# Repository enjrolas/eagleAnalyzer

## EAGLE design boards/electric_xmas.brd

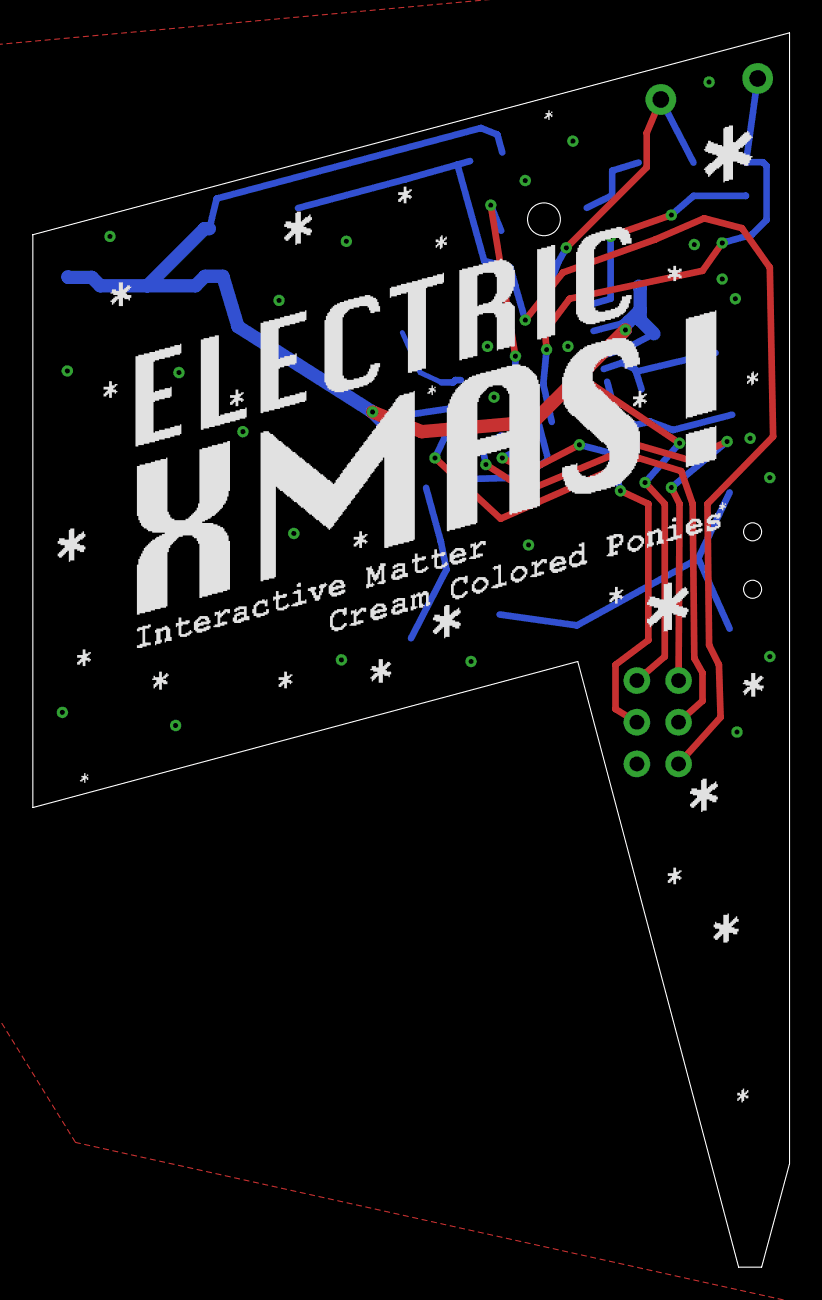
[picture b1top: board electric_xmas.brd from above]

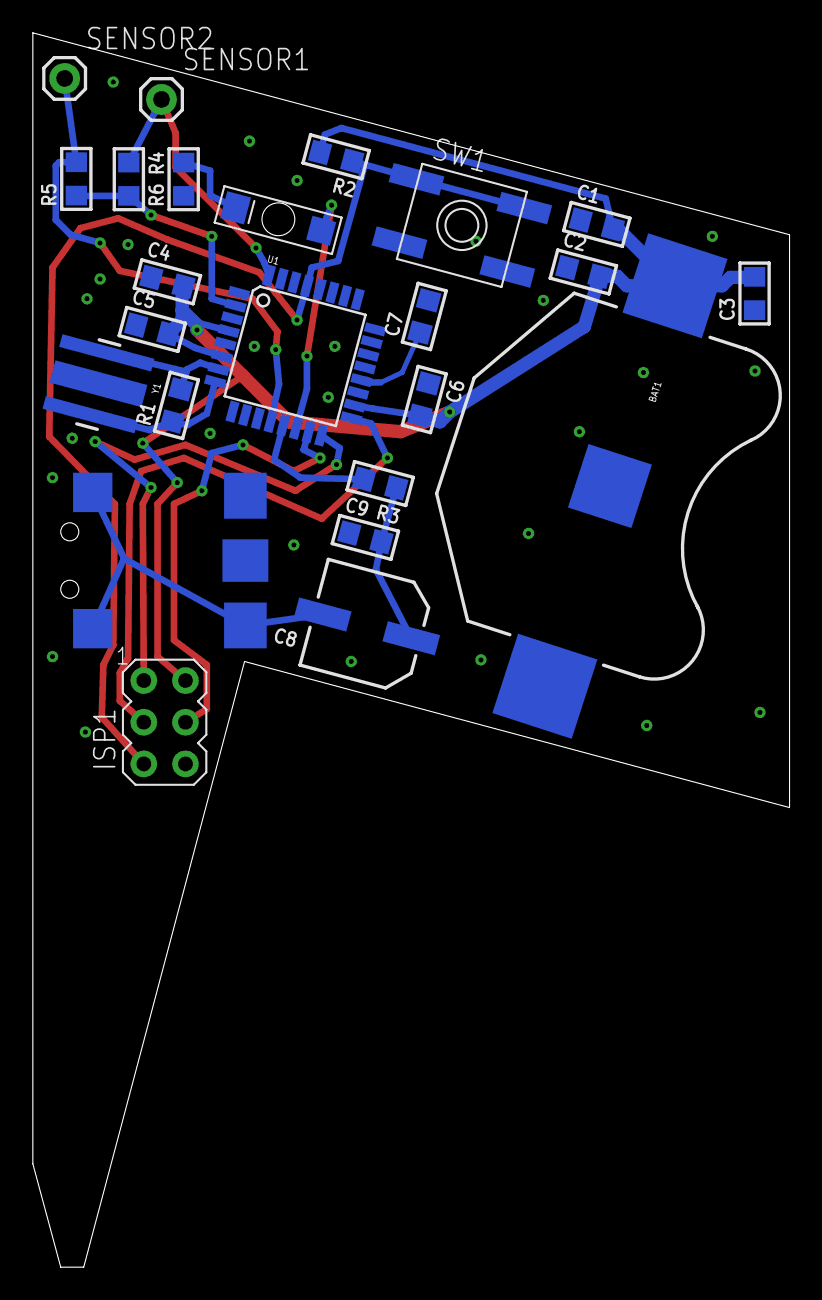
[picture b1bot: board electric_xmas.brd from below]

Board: 2 copper layers, 46.1 x 75.2 mm, 26 parts (24 on the bottom side), 17 nets.

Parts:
BAT1: BATTCON_20MM
C1, C2, C3: 10µF; C0805
C4, C5, C6, C7, C9: 100nF; C0805
C8: 100µF; CSV-D
ISP1: AVRISP-6; AVRISP
LED1: LUMEX_GW_BOTTOM
R1: 1M; R0805
R2: 10k; R0805
R3, R6: 2k2; R0805
R4, R5: 3M3; R0805
SENSOR1, SENSOR2: M01PTH; 1X01
SW1: EVQQ2; EVQ-Q2
U1: ATMEGA328P; TQFP32-08
U2: LUMBERGRC-5325A
U$2: OUTLINE
U$3: PRINT
Y1: RESONATORSMD; RESONATOR-SMD

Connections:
!RESET: ISP1.5, R2.1, SW1.B, SW1.B', U1.29
GND: BAT1.2, C1.1, C2.1, C3.1, C4.1, C5.1, C6.1, C7.2, C9.1, ISP1.6, R6.1, SW1.A, SW1.A', U1.3, U1.5, U1.21, U2.1, U2.2, Y1.2
LED: LED1.A, U1.14
MISO: ISP1.1, U1.16
MOSI: ISP1.4, U1.15
unnamed: R1.2, U1.7, Y1.1
unnamed: R1.1, U1.8, Y1.3
unnamed: LED1.C, R6.2
unnamed: C8.-, U2.3, U2.4@1, U2.4@2
unnamed: C7.1, U1.20
unnamed: C8.+, C9.2, R3.1
SCK: ISP1.3, U1.17
SENSOR1: R4.1, SENSOR1.1, U1.32
SENSOR2: R5.2, SENSOR2.1, U1.12
SENSOR_C: R4.2, R5.1, U1.2
SOUND_OUT: R3.2, U1.13
VCC: BAT1.1, C1.2, C2.2, C3.2, C4.2, C5.2, C6.2, ISP1.2, R2.2, U1.4, U1.6, U1.18

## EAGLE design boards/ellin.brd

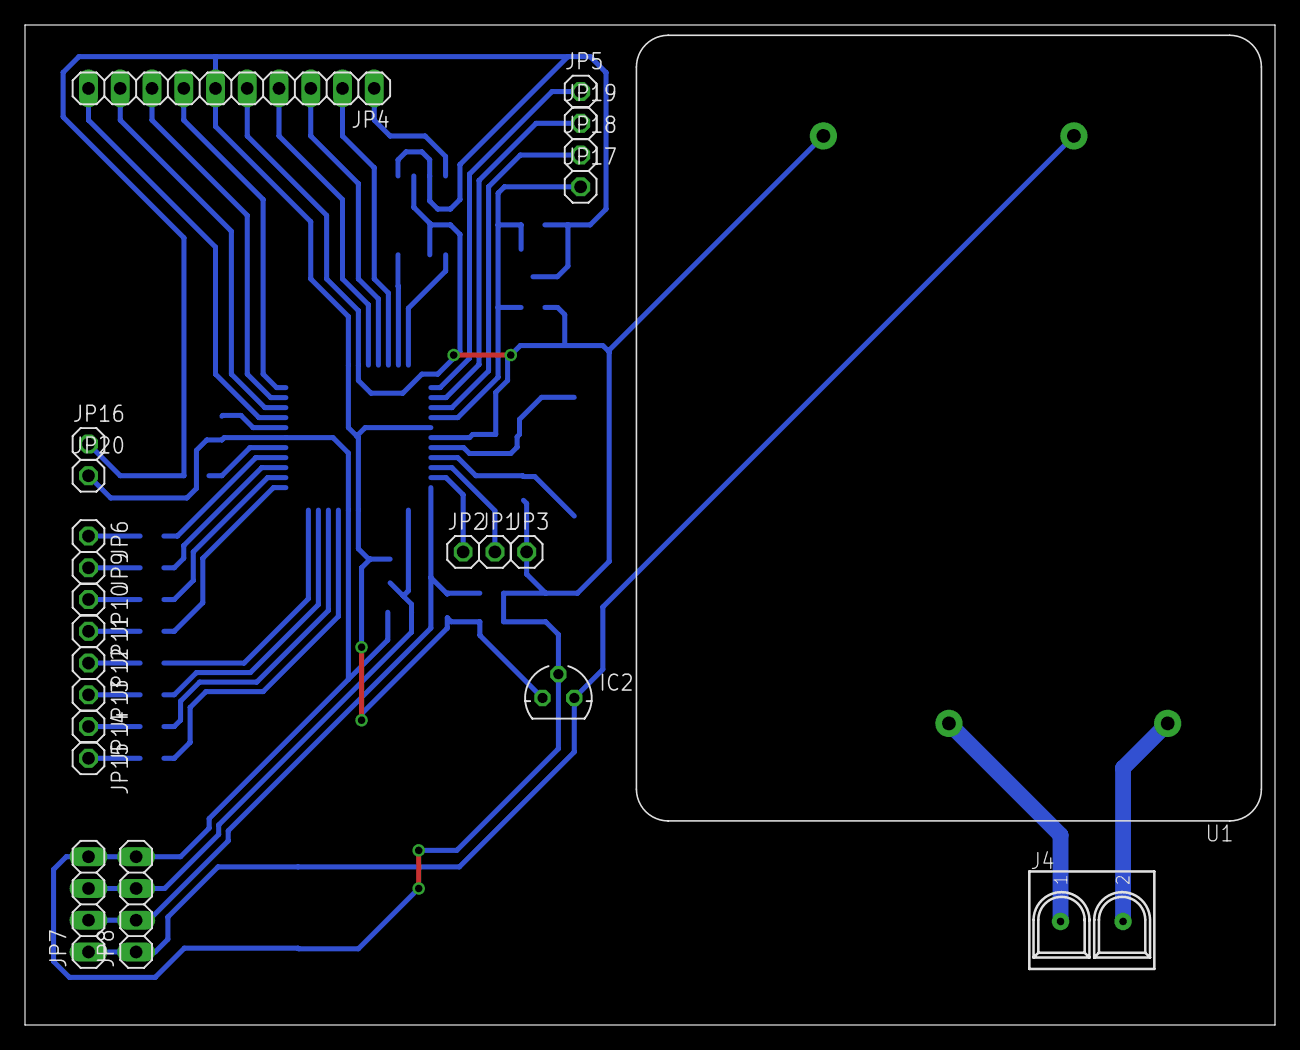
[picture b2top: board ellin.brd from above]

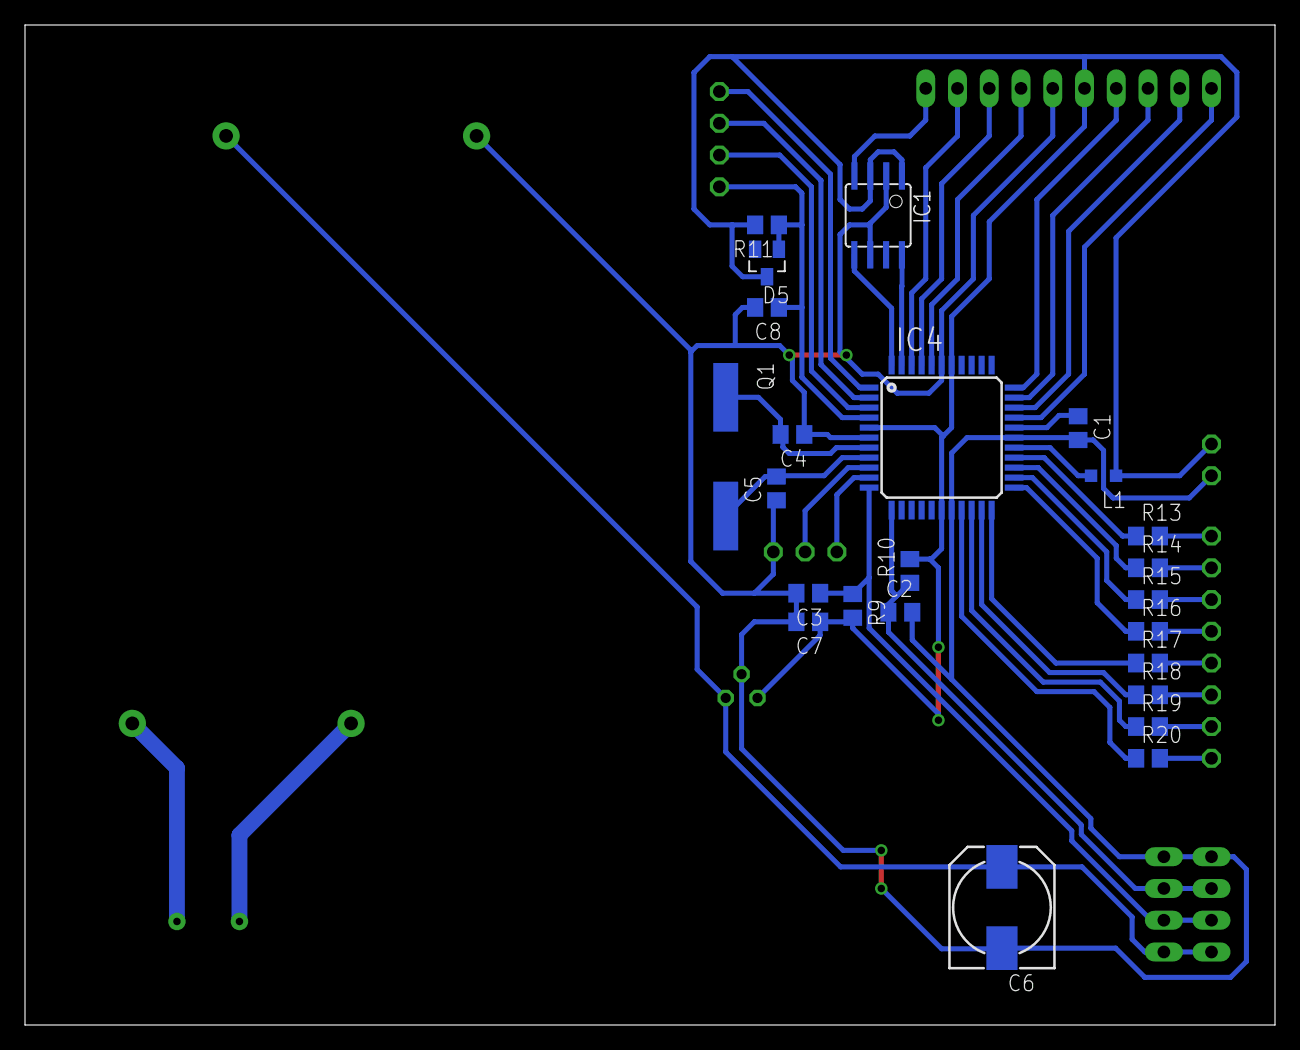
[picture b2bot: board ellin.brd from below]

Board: 2 copper layers, 100.0 x 80.0 mm, 47 parts (24 on the bottom side), 43 nets.

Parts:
C1, C8: 0.1uF; C0805
C2, C3, C7: 22nF; C0805
C4, C5: 22pF; C0805
C6: 10uF; 140CLH-0810
D5: BAS16; SOT23
IC1: MCP4011; SOIC8
IC2: 78L05; 78LXX
IC4: MEGA16-A; TQFP44
J4: DG126-5.0
JP1: RXD; 1X01
JP2: TXD; 1X01
JP3: GND; 1X01
JP4: LCD; 1X10
JP5, JP6, JP9, JP10, JP11, JP12, JP13, JP14, JP15, JP16, JP17, JP18, JP19, JP20: 1X01
JP7, JP8: 1X04
L1: L2012C
Q1: 20MHz; CSM-7X-DU
R9, R10, R11: 10k; R0805
R13, R14, R15, R16, R17, R18, R19, R20: 100; R0805
U1: PM-05

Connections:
+12V: C6.+, IC2.IN, JP7.1, JP8.1, U1.V+
AREF: C1.1, IC4.29
AVCC: IC4.27, L1.2
DATA4: IC4.23, R16.1
DATA5: IC4.24, R15.1
DATA6: IC4.25, R14.1
DATA7: IC4.26, R13.1
DB4: IC4.33, JP4.7
DB5: IC4.32, JP4.8
DB6: IC4.31, JP4.9
DB7: IC4.30, JP4.10
DIG_POT: IC1.8, IC4.43
EN: IC4.40, JP4.4
GND: C1.2, C2.2, C3.2, C4.1, C5.1, C6.-, C7.2, C8.2, IC1.2, IC1.6, IC2.GND, IC4.6, IC4.18, IC4.28, IC4.39, JP3.1, JP4.5, JP7.4, JP8.4, JP20.1, U1.V-
KEYB0: IC4.19, R20.1
KEYB1: IC4.20, R19.1
KEYB2: IC4.21, R18.1
KEYB3: IC4.22, R17.1
MISO: IC4.2, JP19.1
MOSI: IC4.1, JP5.1
unnamed: JP6.1, R13.2
unnamed: J4.1, U1.AC/N
unnamed: J4.2, U1.AC/L
unnamed: JP9.1, R14.2
unnamed: JP10.1, R15.2
unnamed: JP11.1, R16.2
unnamed: JP12.1, R17.2
unnamed: JP13.1, R18.2
unnamed: JP14.1, R19.2
unnamed: JP15.1, R20.2
PHASE_A: C3.1, IC4.11, JP7.2, JP8.2, R9.1
PHASE_B: C2.1, IC4.12, JP7.3, JP8.3, R10.1
POT_CS: IC1.5, IC4.44
R/!W!: IC4.41, JP4.3
RS: IC4.42, JP4.2
RST: C8.1, D5.1, IC4.4, JP17.1, R11.1
RXD: IC4.9, JP1.1
SCK: IC4.3, JP18.1
TXD: IC4.10, JP2.1
VCC: C7.1, D5.3, IC1.1, IC1.3, IC2.OUT, IC4.5, IC4.17, IC4.38, JP4.6, JP16.1, L1.1, R9.2, R10.2, R11.2
W: IC1.4, JP4.1
XTAL1: C5.2, IC4.8, Q1.2
XTAL2: C4.2, IC4.7, Q1.1

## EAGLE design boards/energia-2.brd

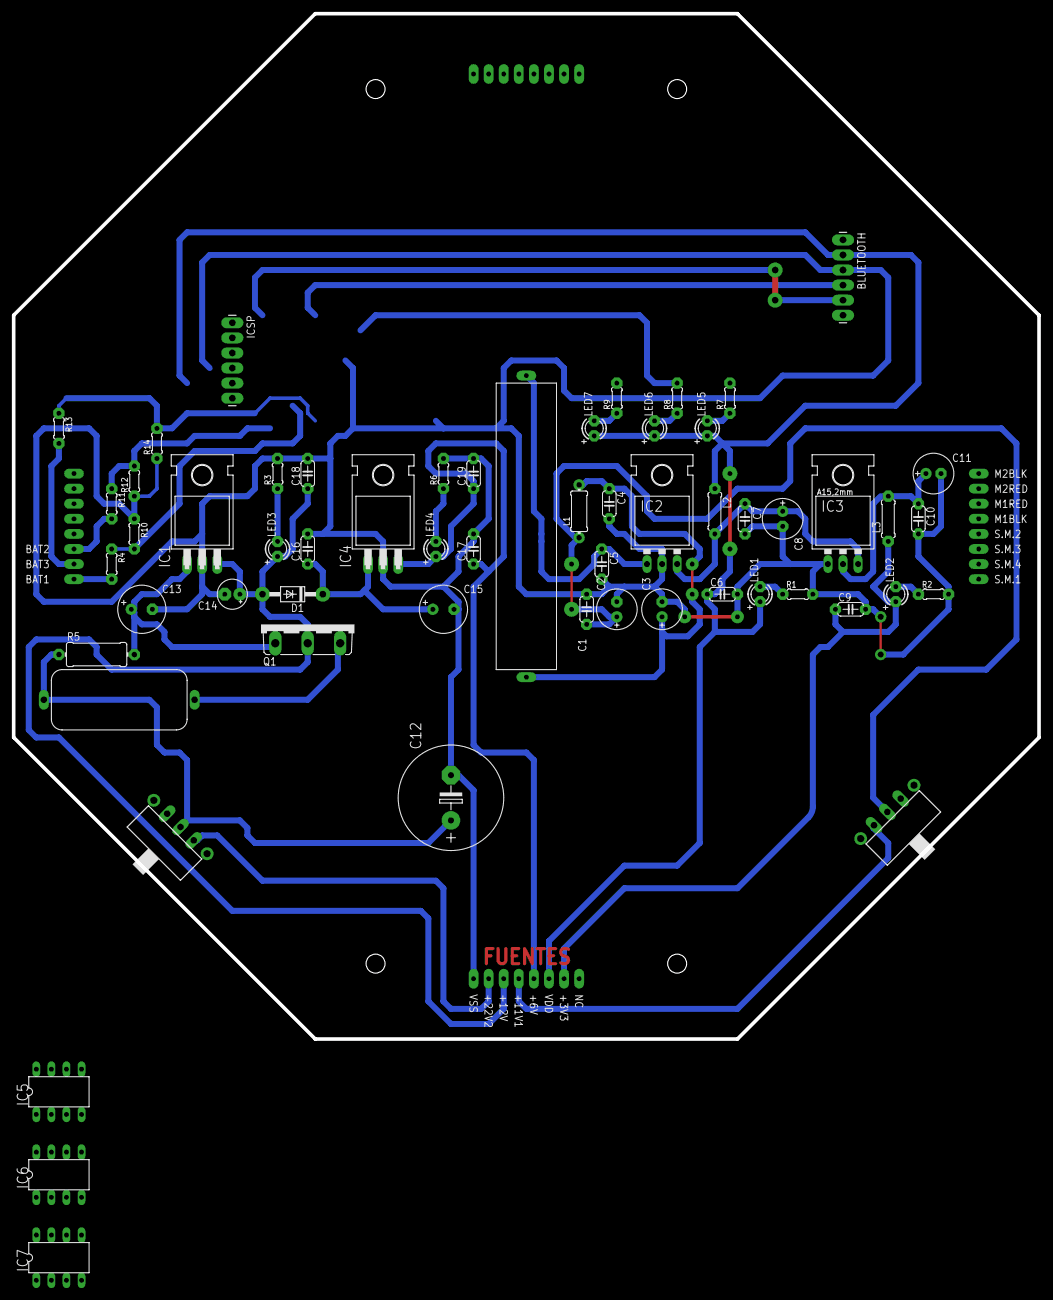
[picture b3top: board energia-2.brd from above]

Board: 2 copper layers, 172.7 x 172.7 mm, 59 parts (0 on the bottom side), 29 nets.

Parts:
BLUETOOTH: 1X06_LONGPADS
C1, C4, C5, C6, C7, C9, C10, C16, C17, C18, C19: 0.1uf; C050-024X044
C2: 470uf; E2,5-7
C3: 100uf; E2,5-7
C8, C11: 22uf; E2,5-7
C12: 3300uf; E7,5-18
C13, C15: 470uf; E3,5-8
C14: 10uf; E2,5-5
D1: 1N4007; DO41-10
IC1: 7812T; TO220H
IC2: 7805; TO-220-ALT
IC3: AZ1117; 78XXL
IC4: 7806T; TO220H
IC5, IC6, IC7: PIC12F675P; DIL8
ICSP: 1X06_LONGPADS
L1: 100uH; TFI0307
L2, L3: 100uH; 0207/7
LED1, LED3: ROJO; LED3MM
LED2, LED4: VERDE; LED3MM
LED5, LED6, LED7: RED; LED3MM
Q1: TIP2955; TOP3AV
R1, R3: 2k2; 0204/5
R2, R6: 680; 0204/5
R4, R11, R13: 20K; 0204/5
R5: 2W100R; 0411/12
R7, R8, R9: 470; 0204/5
R10, R12, R14: 15K; 0204/5
S1, S2: SWITCH; TL3XYO
U$1: BASE
U$6: 5W0.1RJ; RES-22X10
U$9: 10W 5R6J; RES-49X10

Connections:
+3V3: C9.1, L3.1, LED2.A, U$1.PIN22
+6V: C17.1, C19.1, IC4.3, LED4.A, U$1.PIN20
+11V1: S1.3, U$1.PIN19
+12V: C14.+, C18.1, D1.A, IC1.3, LED3.A, Q1.C, U$1.PIN18
+22V: S2.1, U$1.PIN17
AN0: R4.1, R10.2
AN1: R11.1, R12.2
AN2: R13.1, R14.2
unnamed: C1.1, C2.+, L1.1, S1.2
unnamed: LED3.K, R3.1
unnamed: C12.+, R5.1, S2.2, U$6.P$1
unnamed: Q1.E, U$6.P$2
unnamed: C13.+, IC1.1, Q1.B, R5.2
unnamed: LED4.K, R6.1
unnamed: C5.1, IC2.IN, U$9.P$2
unnamed: C3.+, C4.1, L1.2, U$9.P$1
unnamed: C7.1, C8.+, IC2.OUT, IC3.OUT, L2.2
unnamed: C15.+, C16.1, D1.C, IC4.1
unnamed: LED1.K, R1.1
unnamed: LED5.K, R7.1
unnamed: LED7.K, R9.1
unnamed: C10.1, C11.+, IC3.GND, L3.2
unnamed: LED2.K, R2.1
unnamed: LED6.K, R8.1
SENSE1: R4.2, U$1.PIN15
SENSE2: R11.2, U$1.PIN13
SENSE3: R13.2, U$1.PIN14
VDD: BLUETOOTH.2, C6.1, IC5.1, IC6.1, IC7.1, L2.1, LED1.A, LED5.A, LED6.A, LED7.A, U$1.PIN21
VSS: BLUETOOTH.3, C1.2, C2.-, C3.-, C4.2, C5.2, C6.2, C7.2, C8.-, C9.2, C10.2, C11.-, C12.-, C13.-, C14.-, C15.-, C16.2, C17.2, C18.2, C19.2, IC1.2, IC2.GND, IC3.IN, IC4.2, IC5.8, IC6.8, IC7.8, R1.2, R2.2, R3.2, R6.2, R10.1, R12.1, R14.1, U$1.PIN16

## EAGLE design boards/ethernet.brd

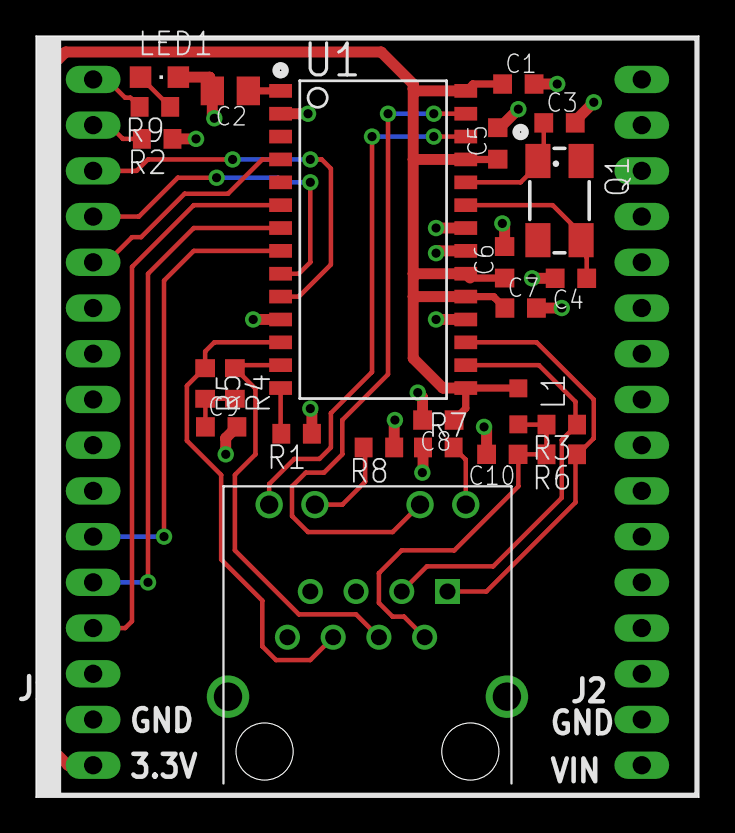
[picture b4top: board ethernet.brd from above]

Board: 2 copper layers, 36.8 x 42.3 mm, 26 parts (0 on the bottom side), 25 nets.

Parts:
C1, C5, C6, C7, C8, C9, C10: 0.1 uF; C0603K
C2: 22 uF; C0805K
C3, C4: 18 pF; C0603K
J1, J2: MA016-1
J3: SI-50154
L1: Ferrite 80mA; L2012C
LED1: Green; CHIPLED_0805
Q1: 25 MHz; CTS406
R1: 2.32k 1%; R0603
R2, R7, R8, R9: 150; R0603
R3, R4, R5, R6: 50; R0603
U1: ENC28J60; SO-28W

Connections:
GND: C1.2, C2.2, C3.2, C4.2, C5.2, C6.2, C7.2, C8.2, C9.2, C10.2, J1.2, J1.8, J2.2, J2.8, J3.P$8, LED1.C, R1.1, R2.1, R7.1, R8.1, U1.2, U1.11, U1.18, U1.21, U1.22
GPIO0: J1.16, R9.2
GPIO1: J1.15, R2.2
GPIO2: J1.14, U1.10
GPIO3: J1.13, U1.9
GPIO4_INT0: J1.12, U1.4
LEDA: J3.P$10, U1.27
LEDA-: J3.P$9, R7.2
LEDB: J3.P$12, U1.26
LEDB-: J3.P$11, R8.2
MISO: J1.4, U1.6
MOSI: J1.5, U1.7
unnamed: LED1.A, R9.1
RBIAS: R1.2, U1.14
SCK: J1.6, U1.8
TCT: C10.1, J3.P$2, L1.2, R3.2, R6.2
TPIN+: J3.P$4, R4.1, U1.13
TPIN-: J3.P$6, R5.1, U1.12
TPIN_CAP: C9.1, R4.2, R5.2
TPOUT+: J3.P$1, R6.1, U1.17
TPOUT-: J3.P$3, R3.1, U1.16
VCAP: C2.1, U1.1
VCC: C1.1, C5.1, C6.1, C7.1, C8.1, J1.1, L1.1, U1.15, U1.19, U1.20, U1.25, U1.28
XTAL3: C3.1, Q1.1, U1.24
XTAL4: C4.1, Q1.3, U1.23

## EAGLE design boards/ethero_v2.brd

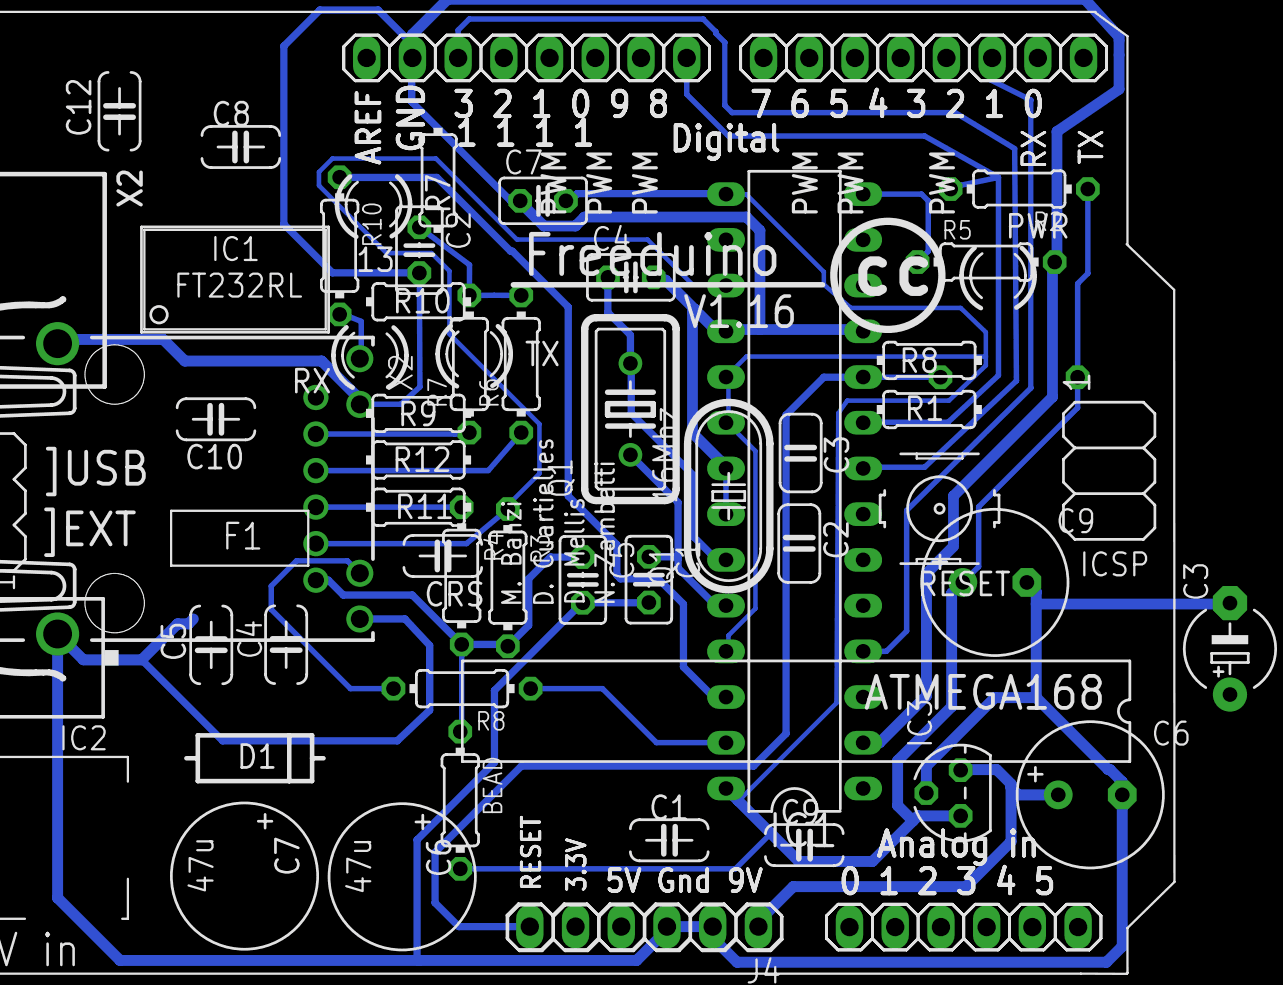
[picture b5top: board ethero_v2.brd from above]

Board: 2 copper layers, 26 parts (1 on the bottom side), 23 nets.

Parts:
BEAD: 18; 0204/7
C1, C4: 18pF; C025-025X050
C2, C5, C7: 100nF; C025-025X050
C3: 10uF; E5-5
C6, C9: 47u; E3,5-8
IC1: ENC28J60SP; DIL28-3
IC3: LP2950Z; TO92
J1, J3: 1X08
J2, J4: 1X06
Q1: HC18U-V
R1, R2: 10k; 0204/7
R3, R4, R6, R7: 50; 0204/7
R5: 2k; 0204/7
R8, R10: 220; 0204/7
X2: JP011821U; JP

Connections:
CT: BEAD.1, C5.1, R3.2, R4.2, X2.1
GND: C1.2, C2.2, C3.-, C4.2, C5.2, C6.-, C7.1, C9.-, IC1.2, IC1.11, IC1.18, IC1.21, IC1.22, IC3.2, J1.7, J4.2, J4.3, R5.2, X2.7, X2.9, X2.SH1, X2.SH2
INT0: IC1.4, J3.3
LEDA: IC1.27, R8.1
LEDB: IC1.26, R10.1
MISO: IC1.6, J1.5
MOSI/OC2: IC1.7, J1.4
unnamed: C2.1, R6.2, R7.2
unnamed: R8.2, X2.8
unnamed: R10.2, X2.10
OSC1: C4.1, IC1.23, Q1.2
OSC2: C1.1, IC1.24, Q1.1
RBIAS: IC1.14, R5.1
RESET: IC1.10, J4.6, R1.2
SCK: IC1.8, J1.6
SS/OC1B: IC1.9, J1.1, R2.2
TPINM: IC1.12, R7.1, X2.5
TPINP: IC1.13, R6.1, X2.4
TPOUTM: IC1.16, R4.1, X2.3
TPOUTP: IC1.17, R3.1, X2.2
V3.3: BEAD.2, C7.2, C9.+, IC1.15, IC1.19, IC1.20, IC1.25, IC1.28, IC3.1, R1.1, R2.1
VCAP: C3.+, IC1.1
VIN: C6.+, IC3.3, J4.1

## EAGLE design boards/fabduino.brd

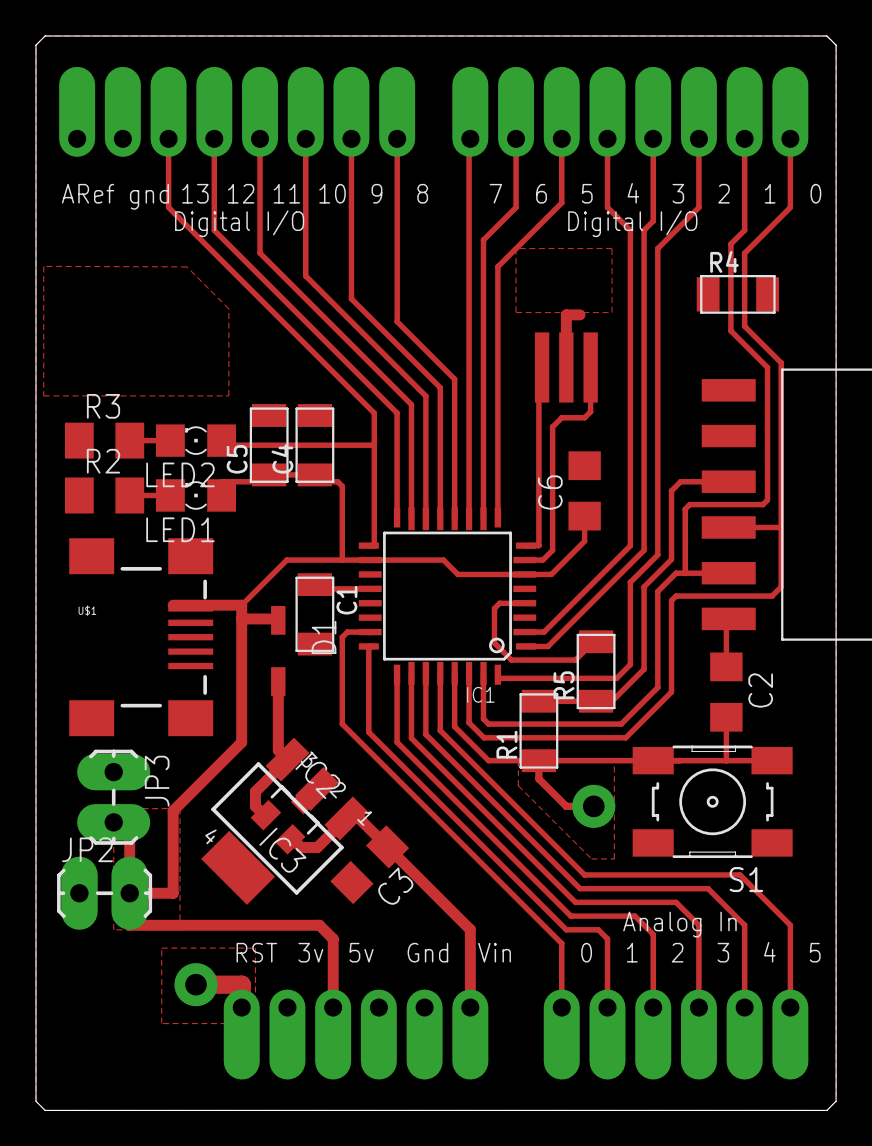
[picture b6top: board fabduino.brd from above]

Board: 2 copper layers, 44.5 x 59.7 mm, 24 parts (0 on the bottom side), 31 nets.

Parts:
C1, C4: 0.1u; C1206FAB
C2, C6: 0.1u; C1206
C3: 10u; C1206
C5: 10u; C1206FAB
D1: SOD123
IC1: ATMEGA168; TQFP32-08THIN
IC2: SOT23
IC3: LM340S; SOT223
J4: ARDUINOOBLONG; ARDUINO-NOHOLE-OBLONG
JP1: 1X06-SMD-FEMALE-V2
JP2, JP3: 1X02_LOCK_LONGPADS
LED1: GRN; 1206
LED2: RED; 1206
R1: 10K; R1206FAB
R2, R3: 499; M1206
R4, R5: 0; R1206FAB
S1: 6MM_SWITCH
U$1: USB_MINIB
X1: 8/16M; EFOBM

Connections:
A0: IC1.23, J4.A0
A1: IC1.24, J4.A1
A2: IC1.25, J4.A2
A3: IC1.26, J4.A3
A4: IC1.27, J4.A4
A5: IC1.28, J4.A5
AREF: C1.1, IC1.20
D2: IC1.32, J4.D2
D3: IC1.1, J4.D3
D4: IC1.2, J4.D4
D5: IC1.9, J4.D5
D6: IC1.10, J4.D6
D7: IC1.11, J4.D7
D8: IC1.12, J4.D8
D9: IC1.13, J4.D9
D10: IC1.14, J4.D10
DTR: C2.1, JP1.6
GND: C1.2, C3.2, C4.2, C5.2, C6.2, IC1.3, IC1.5, IC1.21, IC2.3, IC3.2, IC3.4, J4.GND, J4.GND1, J4.GND2, JP1.1, JP1.2, JP2.1, JP3.1, R2.1, R3.1, R4.1, R4.2, S1.1, S1.2, U$1.GND, U$1.SHIELD@1, U$1.SHIELD@2, U$1.SHIELD@3, U$1.SHIELD@4, X1.2
MISO: IC1.16, J4.D12
MOSI: IC1.15, J4.D11
unnamed: IC1.7, X1.1
unnamed: D1.ANODE, IC2.1, IC3.3
unnamed: IC1.8, X1.3
unnamed: LED1.C, R2.2
unnamed: LED2.C, R3.2
RST: C2.2, IC1.29, J4.RESET, R1.1, S1.3, S1.4
RXI: IC1.30, J4.D0, JP1.4
SCK: IC1.17, J4.D13, LED2.A
TXO: IC1.31, J4.D1, JP1.5
VCC: C4.1, C5.1, C6.1, D1.CATHODE, IC1.4, IC1.6, IC1.18, J4.5V, JP1.3, JP2.2, JP3.2, LED1.A, R1.2, R5.1, R5.2, U$1.VBUS
VIN: C3.1, IC2.2, IC3.1, J4.VIN

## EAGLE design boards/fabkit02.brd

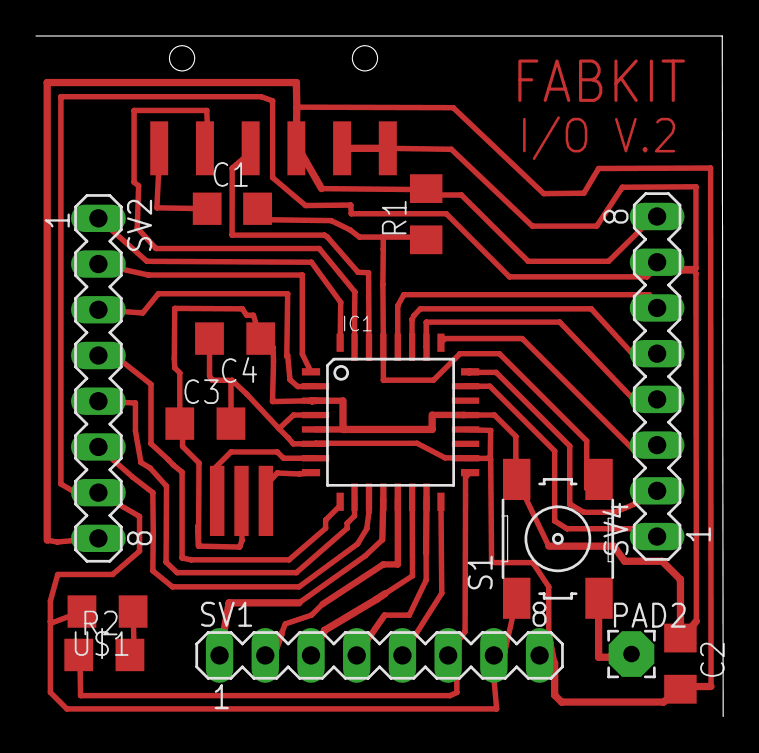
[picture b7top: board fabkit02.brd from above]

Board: 2 copper layers, 38.2 x 37.8 mm, 15 parts (0 on the bottom side), 27 nets.

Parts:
C1: .1uf; C1206
C2: 1uf; 1206
C3: .1uf; 1206
C4: 10uf; 1206
IC1: ATMEGA48/88/168-AU; TQFP32-08
JP1: 1X06-SMD
PAD2: WIREPAD2,54/0,9; 2,54/0,9
R1: 10k; 1206
R2: 499; 1206
S1: 6MM_SWITCH
SV1, SV2, SV4: MA08-1
U$1: 1206
U$2: RESONATOREFOB; EFOBM

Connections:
DTR: C1.1, JP1.6
GND: C2.1, C3.1, C4.1, IC1.3, IC1.5, IC1.21, JP1.1, JP1.2, S1.1, S1.2, SV1.7, SV2.7, SV4.7, U$1.2, U$2.2
MISO: IC1.16, SV1.5
MOSI: IC1.15, SV1.4
unnamed: IC1.8, U$2.1
unnamed: IC1.12, SV1.1
unnamed: IC1.23, SV4.1
unnamed: IC1.24, SV4.2
unnamed: IC1.25, SV4.3
unnamed: IC1.26, SV4.4
unnamed: IC1.27, SV4.5
unnamed: IC1.28, SV4.6
unnamed: IC1.7, U$2.3
unnamed: IC1.32, SV2.1
unnamed: IC1.1, SV2.2
unnamed: IC1.2, SV2.3
unnamed: IC1.9, SV2.4
unnamed: IC1.10, SV2.5
unnamed: IC1.11, SV2.6
unnamed: IC1.13, SV1.2
unnamed: IC1.14, SV1.3
unnamed: R2.2, U$1.1
RST: C1.2, IC1.29, PAD2.1, R1.1, S1.3, S1.4
RX: IC1.30, JP1.4
SCK: IC1.17, R2.1, SV1.6
TX: IC1.31, JP1.5
VCC: C2.2, C3.2, C4.2, IC1.4, IC1.6, IC1.18, IC1.20, JP1.3, R1.2, SV1.8, SV2.8, SV4.8

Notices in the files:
boards/electric_xmas.brd:
This work is licensed under a
Creative Commons Attribution 3.0 Germany License.
parts and their libraries:
rc-master-smd: Copyright (C) 2007, Bob Starr
SparkFun: Licensing: CC v3.0 Share-Alike You are welcome to use this library for commercial purposes.
